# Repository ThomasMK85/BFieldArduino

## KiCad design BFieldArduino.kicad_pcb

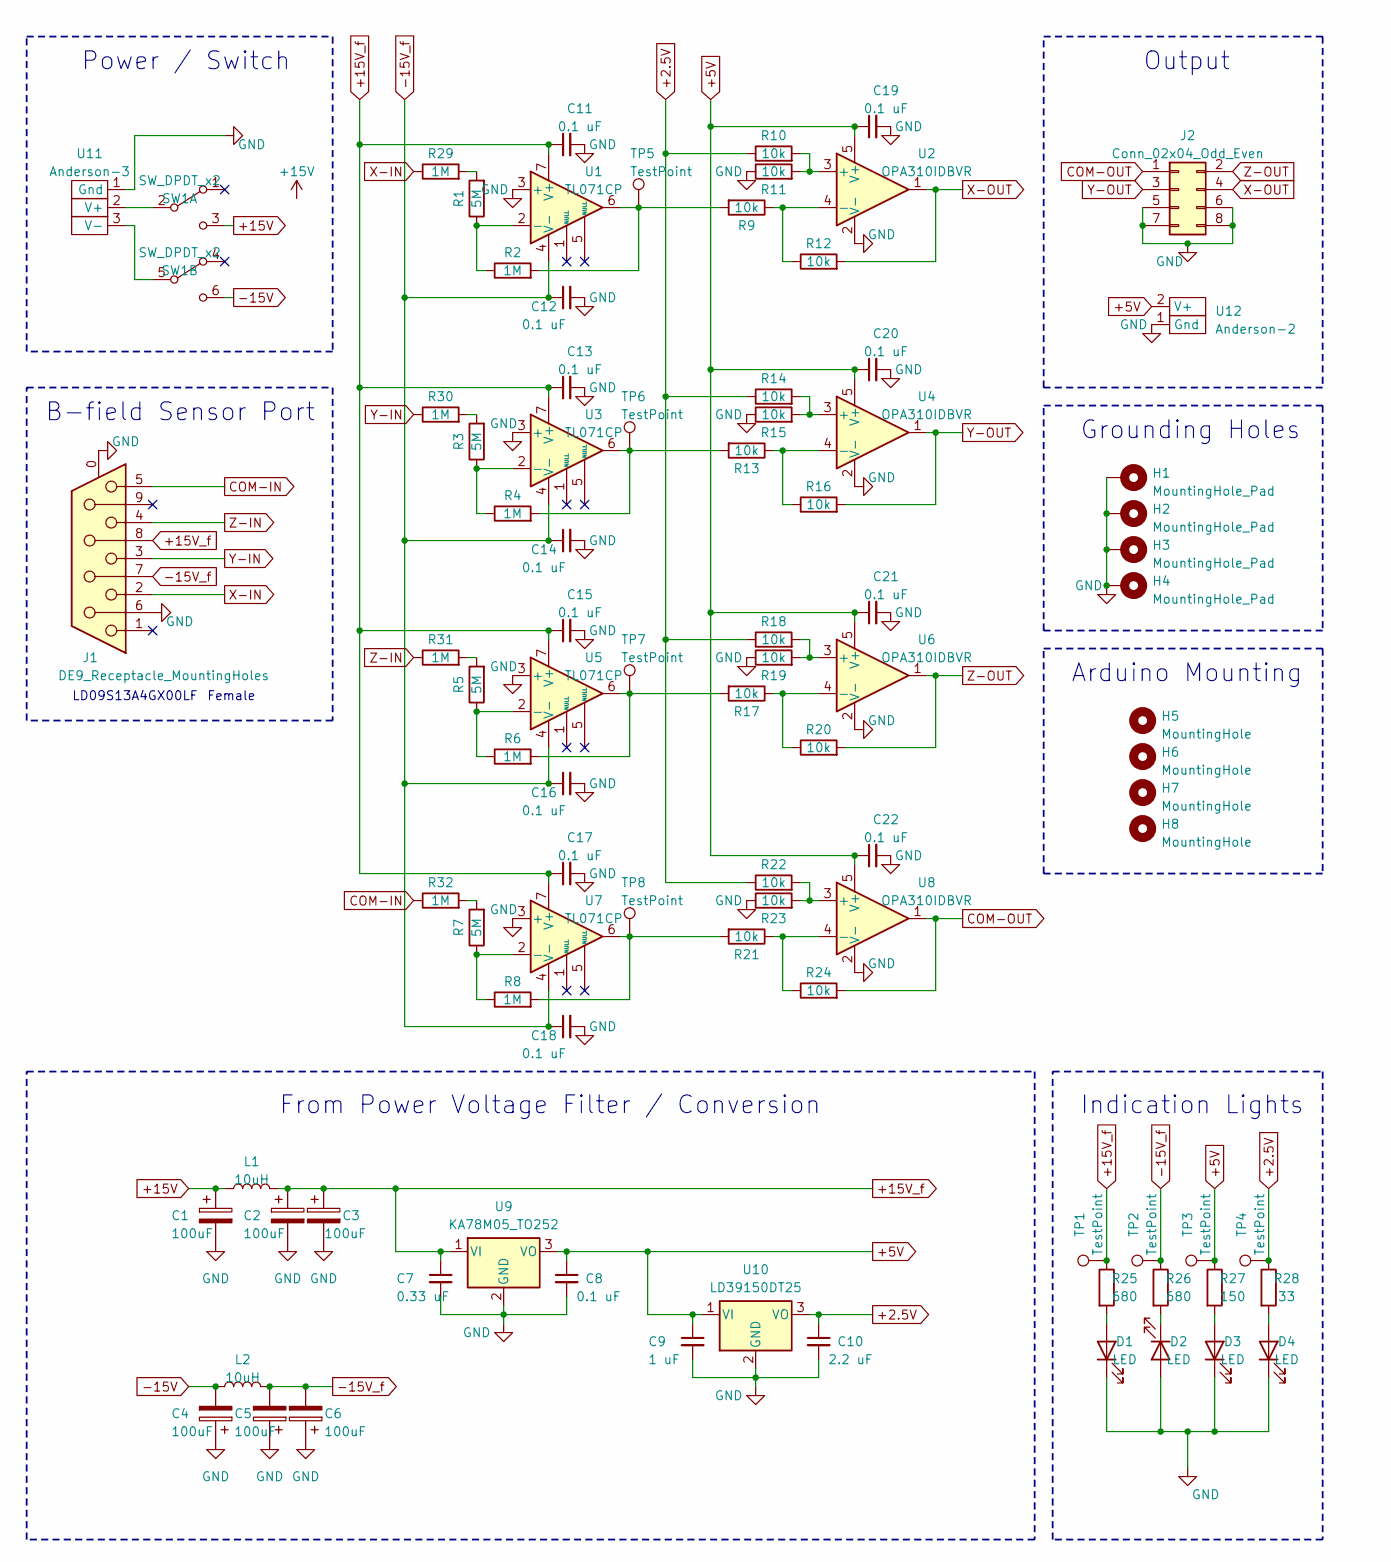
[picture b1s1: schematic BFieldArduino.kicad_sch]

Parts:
C1, C2, C3, C4, C5, C6: 100uF; CP_Radial_D6.3mm_P2.50mm
C7: 0.33 uF; C_Disc_D5.0mm_W2.5mm_P5.00mm
C8, C11, C12, C13, C14, C15, C16, C17, C18, C19, C20, C21, C22: 0.1 uF; C_Disc_D5.0mm_W2.5mm_P5.00mm
C9: 1 uF; CP_Radial_D5.0mm_P2.00mm
C10: 2.2 uF; CP_Radial_D4.0mm_P2.00mm
D1, D2, D3, D4: LED; LED_0201_0603Metric
H1, H2, H3, H4: MountingHole_Pad; MountingHole_5mm_Pad
H5, H6, H7, H8: MountingHole; MountingHole_3mm
J1: DE9_Receptacle_MountingHoles; DSUB-9_Female_Horizontal_P2.77x2.84mm_EdgePinOffset9.90mm_H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
J2: Conn_02x04_Odd_Even; Molex_Micro-Fit_3.0_43045-0812_2x04_P3.00mm_Vertical
L1, L2: 10uH; L_Radial_D8.7mm_P5.00mm_Fastron_07HCP
R1, R3, R5, R7: 5M; R_Axial_DIN0411_L9.9mm_D3.6mm_P15.24mm_Horizontal
R2, R4, R6, R8, R29, R30, R31, R32: 1M; R_Axial_DIN0207_L6.3mm_D2.5mm_P10.16mm_Horizontal
R9, R10, R11, R12, R13, R14, R15, R16, R17, R18, R19, R20, R21, R22, R23, R24: 10k; R_Axial_DIN0207_L6.3mm_D2.5mm_P10.16mm_Horizontal
R25, R26: 680; R_Axial_DIN0414_L11.9mm_D4.5mm_P20.32mm_Horizontal
R27: 150; R_Axial_DIN0414_L11.9mm_D4.5mm_P20.32mm_Horizontal
R28: 33; R_Axial_DIN0414_L11.9mm_D4.5mm_P20.32mm_Horizontal
SW1: SW_DPDT_x2; SW_E-Switch_100DP1T1B1M2QEH_DPDT_Toggle_Straight
TP1, TP2, TP3, TP4, TP5, TP6, TP7, TP8: TestPoint; TestPoint_Loop_D2.50mm_Drill1.0mm
U1, U3, U5, U7: TL071CP; DIP-8_W7.62mm
U2, U4, U6, U8: OPA310IDBVR; SOT-23-5
U9: KA78M05_TO252; TO-252-2
U10: LD39150DT25; TO-252-3_TabPin2
U11: Anderson-3; Anderson_3_Horizontal_Side_by_Side
U12: Anderson-2; Anderson_2_Horizontal_Side_by_Side

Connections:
+2.5V: C10.1, R10.1, R14.1, R18.1, R22.1, R28.1, TP4.1, U10.3 (VO)
+5V: C8.1, C9.1, C19.1, C20.1, C21.1, C22.1, R27.1, TP3.1, U2.5 (V+), U4.5 (V+), U6.5 (V+), U8.5 (V+), U9.3 (VO), U10.1 (VI), U12.2 (V+)
+15V: C1.1, L1.1, SW1.3 (C)
+15V_f: C2.1, C3.1, C7.1, C11.1, C13.1, C15.1, C17.1, J1.8, L1.2, R25.1, TP1.1, U1.7 (V+), U3.7 (V+), U5.7 (V+), U7.7 (V+), U9.1 (VI)
-15V: C4.2, L2.1, SW1.6 (C)
-15V_f: C5.2, C6.2, C12.1, C14.1, C16.1, C18.1, J1.7, L2.2, R26.1, TP2.1, U1.4 (V-), U3.4 (V-), U5.4 (V-), U7.4 (V-)
COM-IN: J1.5, R32.1
COM-OUT: J2.1, R24.2, U8.1
GND: C1.2, C2.2, C3.2, C4.1, C5.1, C6.1, C7.2, C8.2, C9.2, C10.2, C11.2, C12.2, C13.2, C14.2, C15.2, C16.2, C17.2, C18.2, C19.2, C20.2, C21.2, C22.2, D1.1 (K), D2.2 (A), D3.1 (K), D4.1 (K), H1.1, H2.1, H3.1, H4.1, J1.0 (PAD), J1.6, J2.5, J2.6, J2.7, J2.8, R11.1, R15.1, R19.1, R23.1, U1.3 (+), U2.2 (V-), U3.3 (+), U4.2 (V-), U5.3 (+), U6.2 (V-), U7.3 (+), U8.2 (V-), U9.2 (GND), U10.2 (GND), U11.1 (Gnd), U12.1 (Gnd)
unnamed: D1.2 (A), R25.2
unnamed: D2.1 (K), R26.2
unnamed: D3.2 (A), R27.2
unnamed: D4.2 (A), R28.2
unnamed: R1.2, R29.2
unnamed: R2.2, R9.2, TP5.1, U1.6
unnamed: R3.2, R30.2
unnamed: R4.2, R13.2, TP6.1, U3.6
unnamed: R6.2, R17.2, TP7.1, U5.6
unnamed: R8.2, R21.2, TP8.1, U7.6
unnamed: R5.2, R31.2
unnamed: R7.2, R32.2
unnamed: SW1.2 (B), U11.2 (V+)
unnamed: SW1.5 (B), U11.3 (V-)
unnamed: R1.1, R2.1, U1.2 (-)
unnamed: R10.2, R11.2, U2.3 (+)
unnamed: R9.1, R12.1, U2.4 (-)
unnamed: R3.1, R4.1, U3.2 (-)
unnamed: R14.2, R15.2, U4.3 (+)
unnamed: R13.1, R16.1, U4.4 (-)
unnamed: R5.1, R6.1, U5.2 (-)
unnamed: R18.2, R19.2, U6.3 (+)
unnamed: R17.1, R20.1, U6.4 (-)
unnamed: R7.1, R8.1, U7.2 (-)
unnamed: R22.2, R23.2, U8.3 (+)
unnamed: R21.1, R24.1, U8.4 (-)
X-IN: J1.2, R29.1
X-OUT: J2.4, R12.2, U2.1
Y-IN: J1.3, R30.1
Y-OUT: J2.3, R16.2, U4.1
Z-IN: J1.4, R31.1
Z-OUT: J2.2, R20.2, U6.1

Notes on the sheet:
Female
Indication Lights
Output
From Power Voltage Filter / Conversion
B-field Sensor Port
Power / Switch
Arduino Mounting
LD09S13A4GX00LF
Grounding Holes

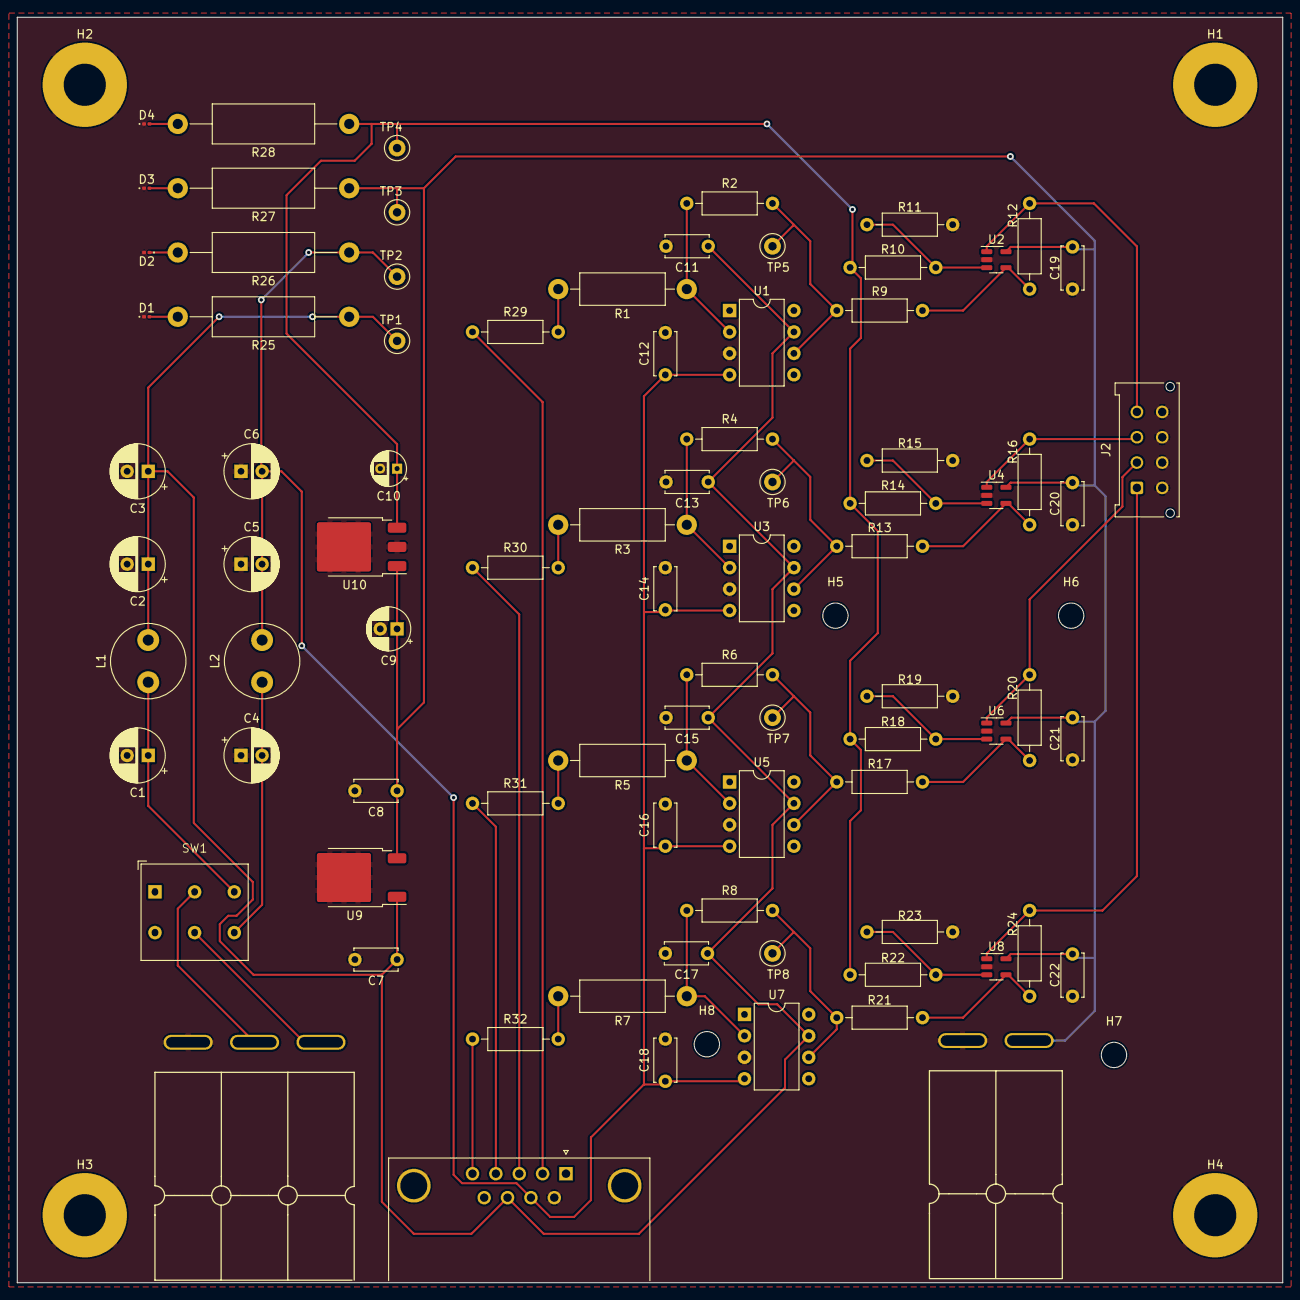
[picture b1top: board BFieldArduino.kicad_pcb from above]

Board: 2 copper layers, 150.0 x 150.0 mm, 91 parts (0 on the bottom side), 41 nets.

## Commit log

2024-05-11 First
2024-06-11 no change
